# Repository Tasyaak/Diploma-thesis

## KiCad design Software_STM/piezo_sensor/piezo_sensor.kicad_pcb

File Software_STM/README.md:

# OscilloscopeSupply
Поддержка дефектоскопии.

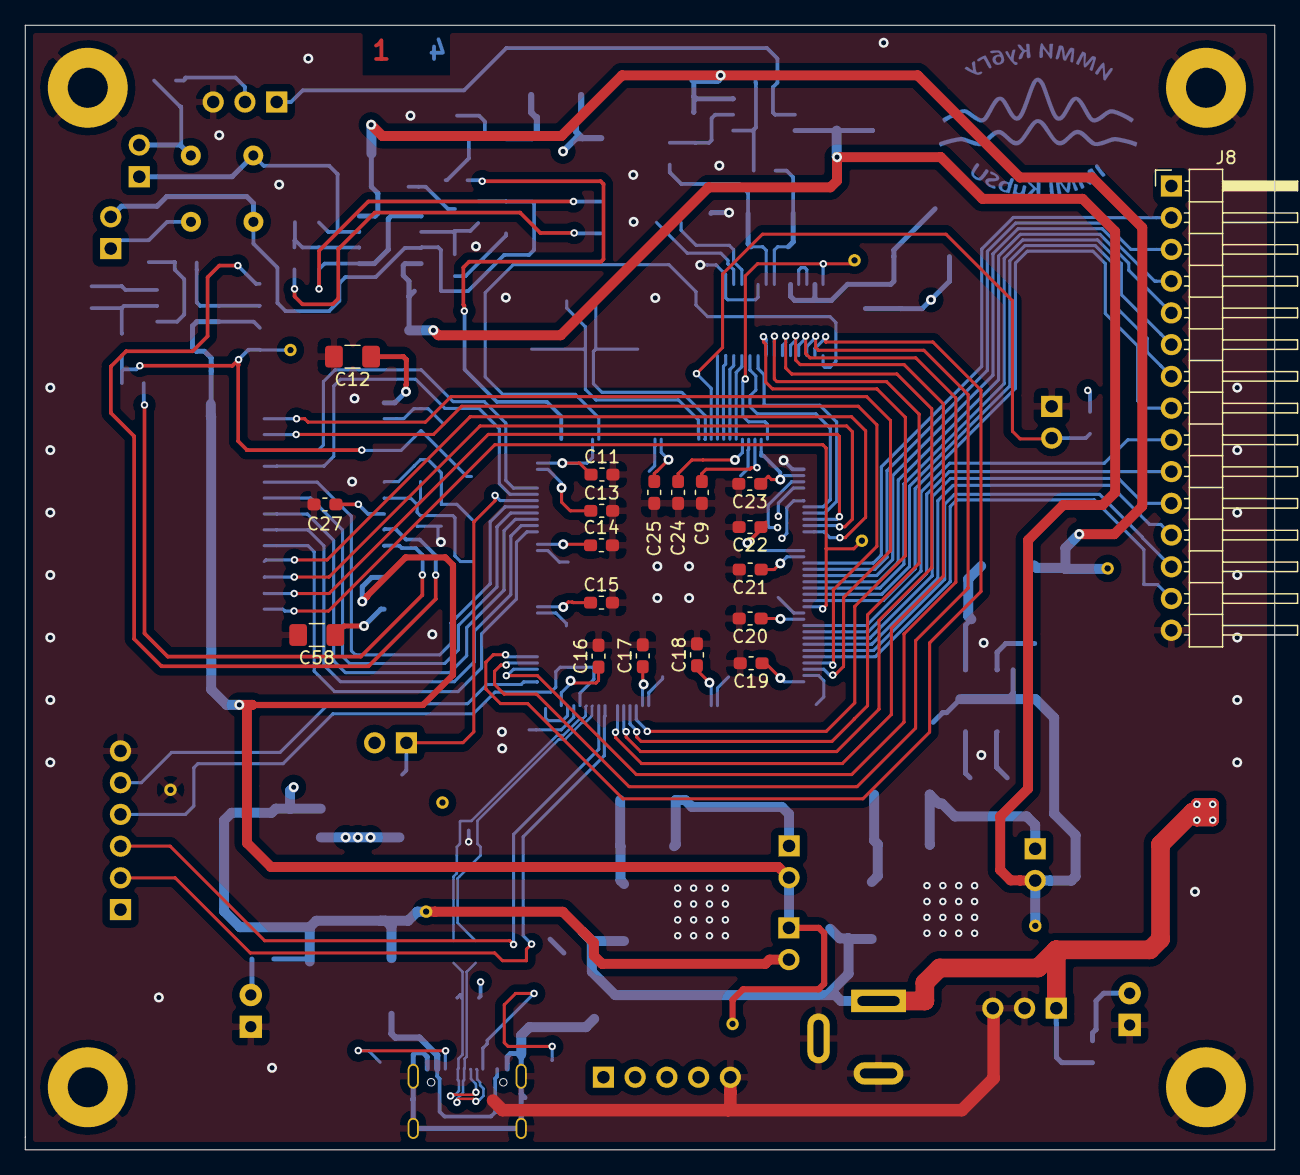
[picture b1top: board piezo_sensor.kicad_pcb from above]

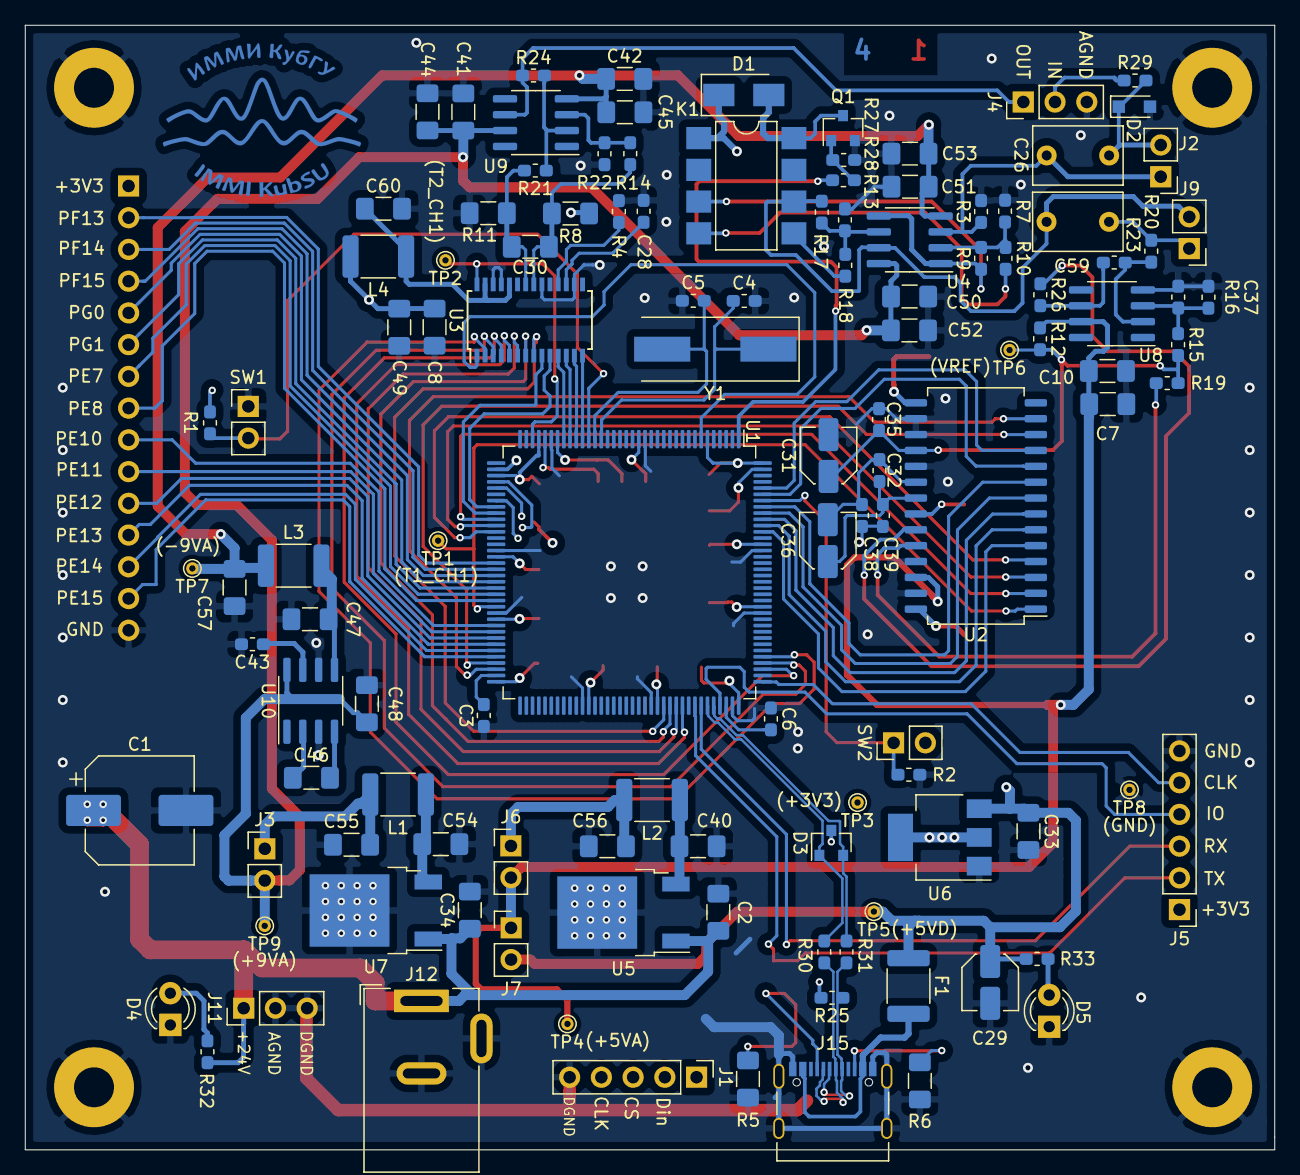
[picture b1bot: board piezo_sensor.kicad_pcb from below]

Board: 4 copper layers, 100.0 x 90.0 mm, 143 parts (120 on the bottom side), 109 nets.

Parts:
C1: CP; CP_Elec_8x10.5
C2, C7, C8, C10, C12, C33, C34, C40, C41, C42, C44, C45, C46, C47, C48, C49, C50, C51, C52, C53, C54, C55, C56, C57, C58, C60: C; C_1206_3216Metric_Pad1.42x1.75mm_HandSolder
C3, C4, C5, C6, C9, C11, C13, C14, C15, C16, C17, C18, C19, C20, C21, C22, C23, C24, C25, C28, C32, C35, C37, C38, C39, C43: C; C_0603_1608Metric_Pad1.05x0.95mm_HandSolder
C26, C59: C; C_Rect_L7.0mm_W4.5mm_P5.00mm
C27: C_Small; C_0603_1608Metric_Pad1.05x0.95mm_HandSolder
C29, C31, C36: CP; C_Elec_4x5.4
C30: C_Small; C_1206_3216Metric_Pad1.42x1.75mm_HandSolder
D1: D; D_SMA
D2: D_TVS; D_SOD-323_HandSoldering
D3: SP0502BAHT; SOT-23
D4, D5: LED; LED_D3.0mm
F1: Fuse_Small; Fuse_1812_4532Metric_Pad1.30x3.40mm_HandSolder
H1, H2, H3, H4: MountingHole_Pad; MountingHole_3.2mm_M3_Pad
J1: Conn_01x05_Male; PinHeader_1x05_P2.54mm_Vertical
J2, J3, J6, J7, J9: Conn_01x02_Male; PinHeader_1x02_P2.54mm_Vertical
J4, J11: Conn_01x03_Male; PinHeader_1x03_P2.54mm_Vertical
J5: Conn_01x06_Male; PinHeader_1x06_P2.54mm_Vertical
J8: Conn_01x15_Male; PinHeader_1x15_P2.54mm_Horizontal
J12: Barrel_Jack_Switch; BarrelJack_Wuerth_6941xx301002
J15: USB_C_Receptacle_USB2.0; USB_C_Receptacle_Palconn_UTC16-G
K1: G6K-2; SMDIP-8_W7.62mm
L1, L2, L3, L4: L; L_1812_4532Metric_Pad1.30x3.40mm_HandSolder
Q1: Q_NMOS_GSD; SOT-23
R1, R2, R3, R7, R9, R10, R12, R13, R14, R15, R16, R17, R18, R19, R20, R21, R22, R23, R24, R25, R26, R27, R28, R29, R30, R31, R32, R33: R; R_0603_1608Metric_Pad1.05x0.95mm_HandSolder
R4: R_Small; R_0603_1608Metric_Pad1.05x0.95mm_HandSolder
R5, R6, R8, R11: R; R_1206_3216Metric_Pad1.42x1.75mm_HandSolder
SW1, SW2: SW_Push; PinHeader_1x02_P2.54mm_Vertical
TP1, TP2, TP3, TP4, TP5, TP6, TP7, TP8, TP9: TestPoint; TestPoint_THTPad_D1.0mm_Drill0.5mm
U1: STM32F407ZGTx; LQFP-144_20x20mm_P0.5mm
U2: AD9220; SOIC-28W_7.5x18.7mm_P1.27mm
U3: AD9744; TSSOP-28_4.4x9.7mm_P0.65mm
U4: AD826; SOIC-8_3.9x4.9mm_P1.27mm
U5: KA78M05_TO252; TO-252-2
U6: LM1117-3.3; SOT-223-3_TabPin2
U7: KA78M09_TO252; TO-252-2
U8, U9: AD8001AR; SOIC-8_3.9x4.9mm_P1.27mm
U10: ICL7660; SOIC-8_3.9x4.9mm_P1.27mm
Y1: Crystal; Crystal_SMD_HC49-SD

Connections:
+3V3: C8.1, C11.1, C13.1, C14.1, C15.1, C16.1, C17.1, C18.1, C19.1, C20.1, C21.1, C22.1, C23.1, C24.1, C25.1, C49.1, C58.1, J5.1, J8.1, L4.2, R1.1, R25.2, SW2.2, TP3.1, U1.6, U1.17, U1.30, U1.33, U1.39, U1.52, U1.62, U1.72, U1.84, U1.95, U1.108, U1.121, U1.131, U1.143, U1.144, U2.28, U6.2
+5VA: C7.1, C10.1, C12.1, J6.2, J7.1, R12.1, TP4.1, U2.15, U2.26, U8.7
+5VD: C29.1, C33.1, D1.1, F1.1, J7.2, K1.1, R33.2, TP5.1, U6.3
+9VA: C41.1, C44.1, C48.1, C50.1, C52.1, J3.2, TP9.1, U4.8, U9.7, U10.8
+24V: C1.1, C2.1, C34.1, J11.1, J12.1, R32.2, U5.1, U7.1
-9VA: C42.2, C45.2, C51.2, C53.2, C57.1, L3.2, TP7.1, U4.4, U9.4
/AIN: C59.1, J9.1, R20.2
/BIT1: U1.70, U2.13
/BIT2: U1.69, U2.12
/BIT3: U1.140, U2.11
/BIT4: U1.139, U2.10
/BIT5: U1.137, U2.9
/BIT6: U1.136, U2.8
/BIT7: U1.135, U2.7
/BIT8: U1.134, U2.6
/BIT9: U1.133, U2.5
/BIT10: U1.48, U2.4
/BIT11: U1.47, U2.3
/BIT12: U1.46, U2.2
/BOOT0: R2.1, SW2.1, U1.138
/CLK: J5.5, U1.109
/CS: J1.3, U1.40
/D+: D3.2, R31.1, U1.104
/D-: D3.1, R30.1, U1.103
/Data: J1.2, U1.43
/IN: J4.2, R29.1
/IND+: J15.A6, J15.B6, R25.1, R31.2
/IND-: J15.A7, J15.B7, R30.2
/IO: J5.4, U1.105
/NRST: R1.2, SW1.2, U1.25
/OUT: J4.1, R24.1, U9.6
/PE7: J8.7, U1.58
/PE8: J8.8, U1.59
/PE10: J8.9, U1.63
/PE11: J8.10, U1.64
/PE12: J8.11, U1.65
/PE13: J8.12, U1.66
/PE14: J8.13, U1.67
/PE15: J8.14, U1.68
/PF13: J8.2, U1.53
/PF14: J8.3, U1.54
/PF15: J8.4, U1.55
/PG0: J8.5, U1.56
/PG1: J8.6, U1.57
/REL: R28.2, U1.1
/RX: J5.3, U1.102
/T1_CH1: TP1.1, U1.60, U2.1
/T2_CH1: TP2.1, U1.34, U3.28
/TX: J5.2, U1.101
/VINA: R26.1, U2.23
/VINB: R19.1, U2.24
/VREF: C31.1, C35.1, R12.2, R15.2, R19.2, TP6.1, U2.18
/sCLK: J1.4, U1.41
GND: C1.2, C2.2, C3.1, C4.2, C5.2, C6.1, C7.2, C8.2, C9.1, C10.2, C11.2, C12.2, C13.2, C14.2, C15.2, C16.2, C17.2, C18.2, C19.2, C20.2, C21.2, C22.2, C23.2, C24.2, C25.2, C27.1, C28.2, C29.2, C31.2, C33.2, C34.2, C35.2, C37.2, C38.1, C39.1, C40.2, C41.2, C42.1, C43.2, C44.2, C45.1, C47.2, C48.2, C49.2, C50.2, C51.1, C52.2, C53.1, C54.2, C55.2, C56.2, C57.2, C58.2, C60.2, D2.2, D3.3, D4.1, D5.1, H1.1, H2.1, H3.1, H4.1, J1.5, J4.3, J5.6, J8.15, J11.2, J11.3, J12.2, J12.3, J15.A1, J15.A12, J15.B1, J15.B12, J15.S1, Q1.2, R2.2, R3.1, R4.2, R5.2, R6.2, R7.1, R8.1, R11.1, R13.1, R16.1, R22.1, R27.1, SW1.1, TP8.1, U1.16, U1.31, U1.38, U1.51, U1.61, U1.83, U1.94, U1.107, U1.120, U1.130, U2.16, U2.17, U2.19, U2.25, U2.27, U3.16, U3.20, U3.25, U3.26, U5.2, U6.1, U7.2, U8.4, U10.3, U10.6
unnamed: C3.2, U1.71
unnamed: C4.1, U1.23, Y1.1
unnamed: C5.1, U1.24, Y1.2
unnamed: C6.2, U1.106
unnamed: C9.2, U1.32
unnamed: C26.1, J2.1, R3.2, U4.3
unnamed: C26.2, D2.1, J2.2, R29.2
unnamed: C27.2, U2.22
unnamed: C28.1, U3.17
unnamed: C30.1, R11.2, R21.2, U3.22
unnamed: C30.2, R8.2, R14.1, U3.21
unnamed: C32.1, C36.2, C38.2, U2.20
unnamed: C32.2, C36.1, C39.2, U2.21
unnamed: C37.1, R15.1, R16.2, U8.3
unnamed: C40.1, L2.1, U5.3
unnamed: C43.1, U10.7
unnamed: C46.1, U10.2
unnamed: C46.2, U10.4
unnamed: C47.1, L3.1, U10.5
unnamed: C54.1, L1.1, U7.3
unnamed: C55.1, J3.1, L1.2
unnamed: C56.1, J6.1, L2.2
unnamed: C59.2, J9.2, K1.6, R17.2, U4.7
unnamed: C60.1, L4.1, U3.24, U3.27
unnamed: D1.2, K1.8, Q1.3
unnamed: D4.2, R32.1
unnamed: D5.2, R33.1
unnamed: F1.2, J15.A4, J15.A9, J15.B4, J15.B9
unnamed: J15.A5, R5.1
unnamed: J15.B5, R6.1
unnamed: K1.3, R9.2, U4.1, U4.5
unnamed: K1.4, R10.2
unnamed: K1.5, R18.2
unnamed: Q1.1, R27.2, R28.1
unnamed: R4.1, U3.18
unnamed: R7.2, R9.1, R10.1, U4.2
unnamed: R13.2, R17.1, R18.1, U4.6
unnamed: R14.2, R22.2, U9.3
unnamed: R20.1, R23.2, U8.2
unnamed: R21.1, R24.2, U9.2
unnamed: R23.1, R26.2, U8.6
unnamed: U1.7, U3.1
unnamed: U1.26, U3.14
unnamed: U1.27, U3.13
unnamed: U1.28, U3.12
unnamed: U1.29, U3.11
unnamed: U1.44, U3.10
unnamed: U1.45, U3.9
unnamed: U1.96, U3.8
unnamed: U1.97, U3.7
unnamed: U1.98, U3.6
unnamed: U1.99, U3.5
unnamed: U1.111, U3.4
unnamed: U1.112, U3.3
unnamed: U1.113, U3.2

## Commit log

2025-11-28 init
2026-02-19 новый init, начало работы с Hantek6074
2026-02-23 API для Hantek готова для тестирования
